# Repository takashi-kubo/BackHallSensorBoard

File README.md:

# BackHallSensorBoard
Backside mounted hall sensor module for CQ Brushless DC Kit motor

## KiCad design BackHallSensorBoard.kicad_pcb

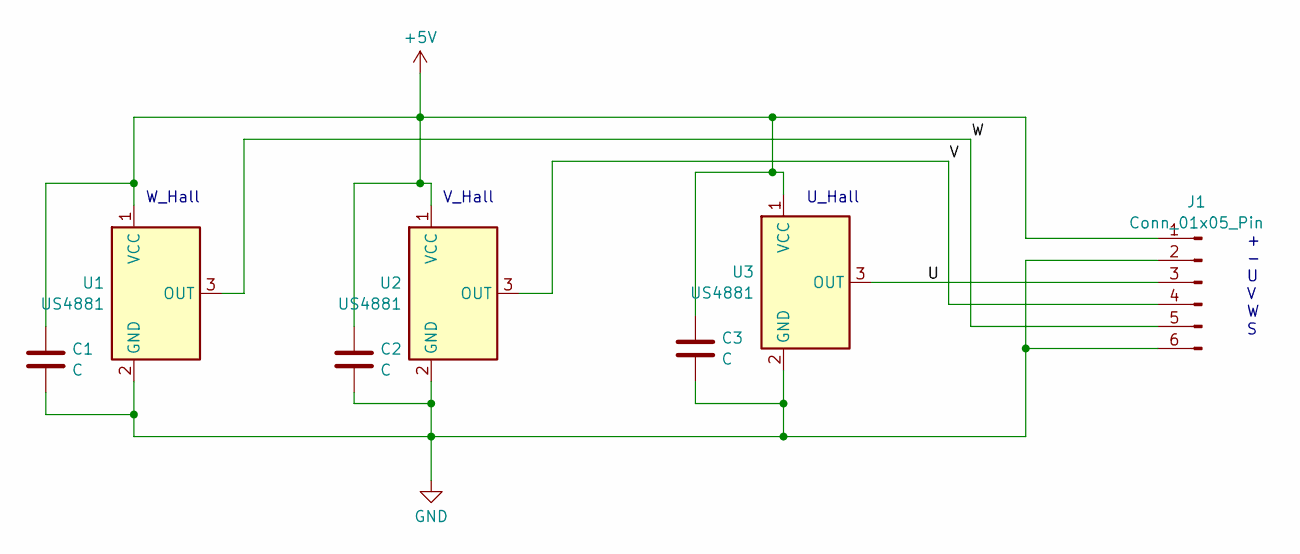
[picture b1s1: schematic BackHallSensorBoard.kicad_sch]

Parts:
C1, C2, C3: C; C_0603_1608Metric_Pad1.08x0.95mm_HandSolder
J1: Conn_01x05_Pin; PinHeader_1x06_P1.27mm_Vertical_SMD_Pin1Left
U1, U2, U3: US4881; PinHeader_1x03_P1.27mm_Vertical_SMD_Pin1Left

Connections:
+5V: C1.1, C2.1, C3.1, J1.1, U1.1 (VCC), U2.1 (VCC), U3.1 (VCC)
/U: J1.3, U3.3 (OUT)
/V: J1.4, U2.3 (OUT)
/W: J1.5, U1.3 (OUT)
GND: C1.2, C2.2, C3.2, J1.2, J1.6, U1.2 (GND), U2.2 (GND), U3.2 (GND)

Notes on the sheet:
W_Hall
U_Hall
+ - U V W S
V_Hall

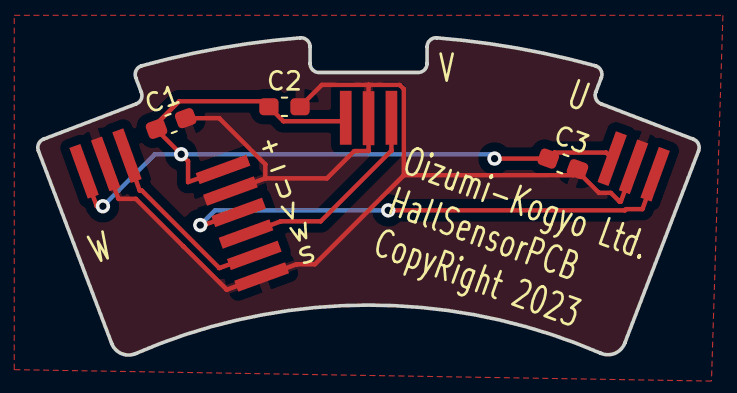
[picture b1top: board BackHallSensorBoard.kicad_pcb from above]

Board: 2 copper layers, 36.7 x 17.6 mm, 7 parts (0 on the bottom side), 5 nets.

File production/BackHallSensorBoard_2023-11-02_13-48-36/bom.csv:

Designator,Footprint,Quantity,Value,LCSC Part #
"C1, C2, C3",0603,3,C,
J1,PinHeader_1x06_P1.27mm_Vertical_SMD_Pin1Left,1,Conn_01x05_Pin,
"U1, U2, U3",PinHeader_1x03_P1.27mm_Vertical_SMD_Pin1Left,3,US4881,

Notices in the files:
BackHallSensorBoard.kicad_pcb:
CopyRight 2023
